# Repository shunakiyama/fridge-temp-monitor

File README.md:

# 🇵🇱 Urządzenie monitorujące temperaturę w lodówce
To oparte na ESP32 urządzenie oferuje monitorowanie wielu stref w twojej lodówce. Temperaturę możesz odczytać lokalnie z wyświetlacza oraz
przez portal webowy lub aplikację HomeAssistent.

## Dlaczego?
Nie każda lodówka jest zbyt dobra albo nie każda jest na tyle nowa aby posiadać termostat. Dzięki temu urządzeniu możesz monitorować i zapisywać 
temperaturę w swojej lodówce aby mieć pewność że utrzymuje temperaturę w bezpiecznych limitach oraz poprawić poziom chłodzenia gdy widzisz że jest 
nie odpowiedni.

Posiadacze dobrych lodówek też mogą skorzystać z tego urządzenia gdyż pozwala na monitorowanie kilku stref naraz, coś co dopiero drogie, high-end, lodówki 
posiadają.

## Pliki
```
|--code
    |--esphome
    |--v3_multiple_sensors
|--models
    |--solidworks
    |--3d_printing
|--pcb
    |--fridge_temp_design
        |--[WSZYSTKIE PLIKI]
    |--gerber

```
Folder ```code``` posiada wszystkie pliki związane z oprogramowaniem. Aktualna wersja, używająca ESPHome, jest w folderze ```esphome```. Wersja C++ (.ino) jest w
```v3_multiple_sensors```.

Folder ```models``` posiada wszystkie pliki związane z obudową. Folder ```solidworks``` posiada wszytskie pliki z programu SolidWorks, otwórz te pliki 
w Soliwroks aby edytować ten design. Folder ```3d_printing``` posiada modele wyeksportowane do ```.stl```, gotowe do druku 3d.

Folder ```pcb/fridge_temp_design``` posiada wszystkie pliki dotyczące PCB.

Folder `pcb/gerber` zawiera wszystkie pliki gerber.

## Plany

Te plany zostały stworzone w oprogramowaniu Fritzing. Ta wersja skupia się wyłącznie na działających częściach komponentu, pomijając szczegóły takie jak zasilanie czy rozwiązania montażowe.

## Wersja 2

Oto jak powinna wyglądać płytka PCB po wlutowaniu większości komponentów (nie ma tu złącz ARK/śrubowych, ponieważ nie udało mi się znaleźć ich modelu). Proszę zwrócić uwagę na specjalne otwory przeznaczone na opaski zaciskowe – przymocują one kable termometrów, zmniejszając naprężenie na złączach.

# 🇬🇧 Fridge temperature monitoring device
This ESP32 based device allows for temperature monitoring in many zones at once in your fridge. You can read the temperature locally or on a HomeAssistant's
webportal or app.

## Why?
Not every fridge is good or new enough to have a thermostat. Thanks to this device you can monitor and record your fridge's temperature and be sure it
keeps itself in the safe limits, adjust it based on the readings.

The owners of good fridges also can use this device as it allows the monitoring of many zones at once which only the expensive, high-end, ones can do.

## Files
```
|--code
    |--esphome
    |--v3_multiple_sensors
|--models
    |--solidworks
    |--3d_printing
|--pcb
    |--fridge_temp_design
        |--[ALL FILES]
    |--gerber
```

Folder ```code``` has all files related to software. Current version, using ESPHome, is in ```esphome```. C++ version (.ino) is in ```v3_multiple_sensors```.

Folder ```models``` has all the files related to the case. Folder ```solidworks``` has all the SolidWorks files, use these files to edit the design.
Folder ```3d_printing``` has all the models exported to ```.stl```, ready to be 3d printed.

Folder ```pcb/fridge_temp_design``` has all files related to the PCB design. 

Folder `pcb/gerber` has all gerber files. 

## Plans

These plans were created in Fritzing software. This version focuses solely on the working parts of the component, omitting details like power delivery or mounting solutions.

## Version 2

This shows how the PCB should look when most of the components are soldered (there are no ARK/screw terminals, as I could not find a model for them). Please notice the special holes designed for zip ties; they will tie down the thermometer cables, reducing the strain on the connectors.

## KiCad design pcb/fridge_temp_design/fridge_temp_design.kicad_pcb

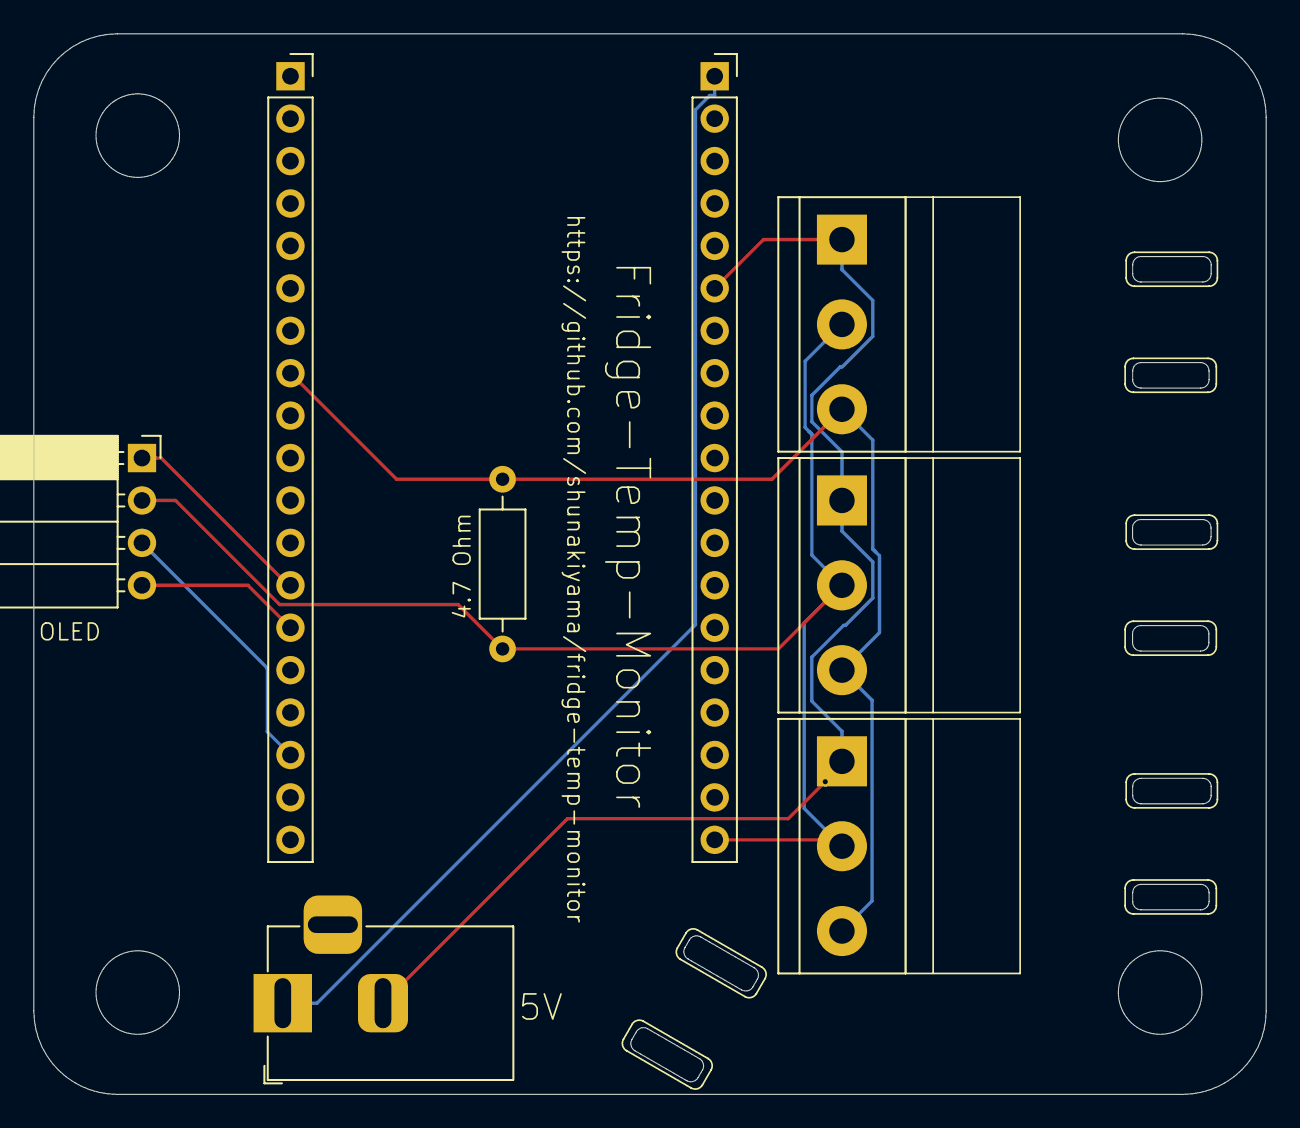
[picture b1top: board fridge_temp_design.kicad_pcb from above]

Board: 2 copper layers, 73.8 x 63.5 mm, 12 parts (0 on the bottom side), 7 nets.

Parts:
Bottom_Left: MountingHole_5mm
Bottom_Right: MountingHole_5mm
J1, J2: ESP32_LEG; PinSocket_1x19_P2.54mm_Vertical
J3, J4, J5: DS18B12; TerminalBlock_bornier-3_P5.08mm
J6: Barrel_Jack_Switch; BarrelJack_Horizontal
J7: OLED; PinSocket_1x04_P2.54mm_Horizontal
R1: 4.7 Ohm; R_Axial_DIN0207_L6.3mm_D2.5mm_P10.16mm_Horizontal
Top_Left: MountingHole_5mm
Top_Right: MountingHole_5mm

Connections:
unnamed: J1.1, J6.1
unnamed: J1.6, J3.1, J4.1, J5.1, J6.2
unnamed: J1.19, J3.2, J4.2, J5.2, J7.2, R1.1
unnamed: J2.8, J3.3, J4.3, J5.3, R1.2
unnamed: J2.13, J7.1
unnamed: J2.14, J7.4
unnamed: J2.17, J7.3

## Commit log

2025-05-06 added kicad project
2025-05-06 yaml and solidworks
2025-05-10 added pics
2025-05-13 swicthing machines
2025-05-25 added_pics
